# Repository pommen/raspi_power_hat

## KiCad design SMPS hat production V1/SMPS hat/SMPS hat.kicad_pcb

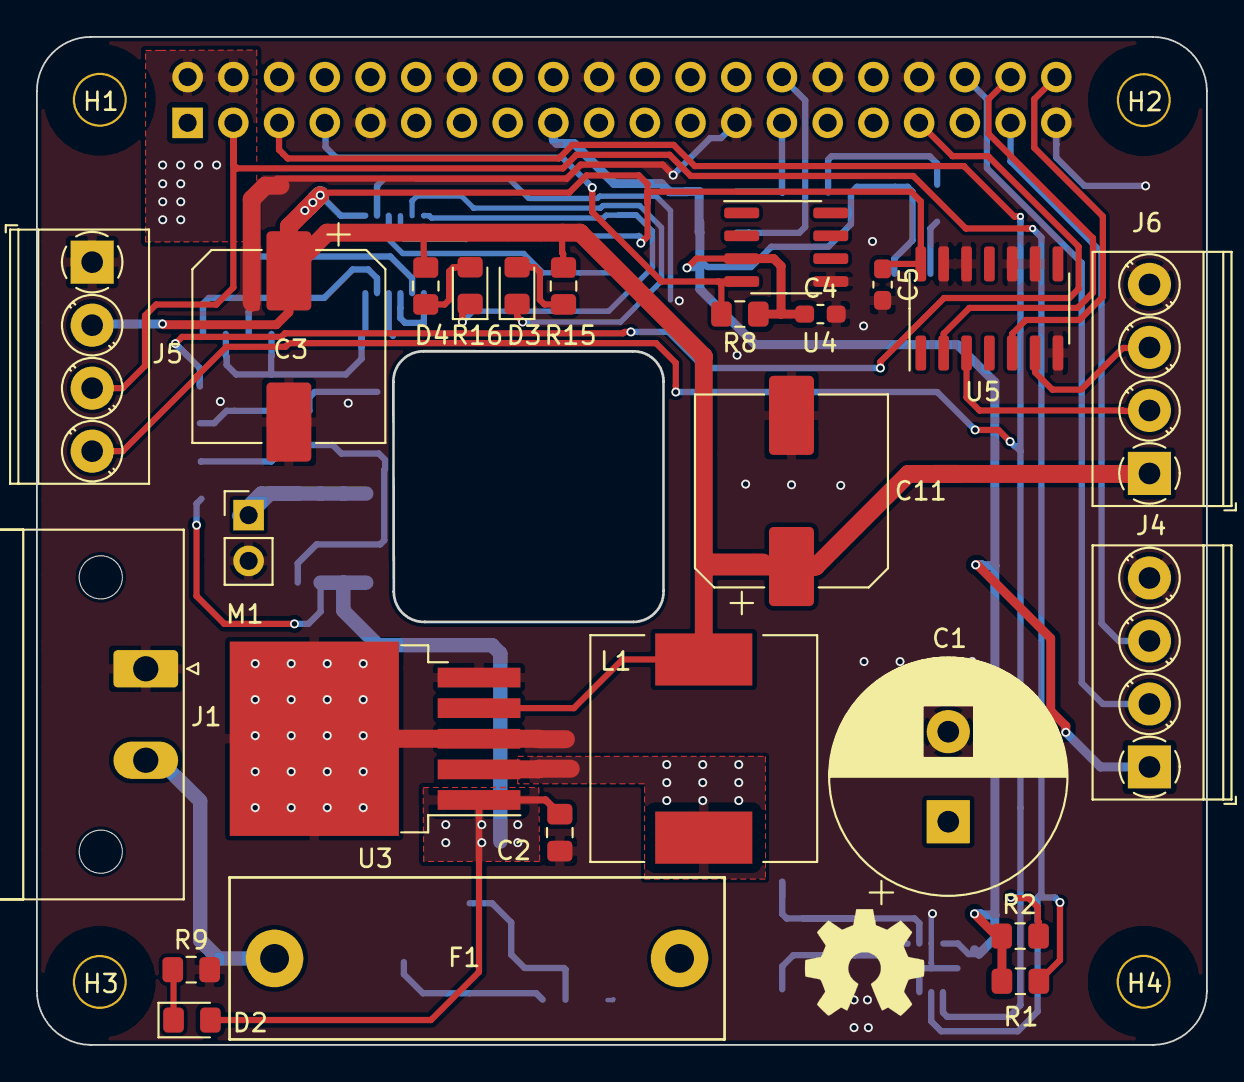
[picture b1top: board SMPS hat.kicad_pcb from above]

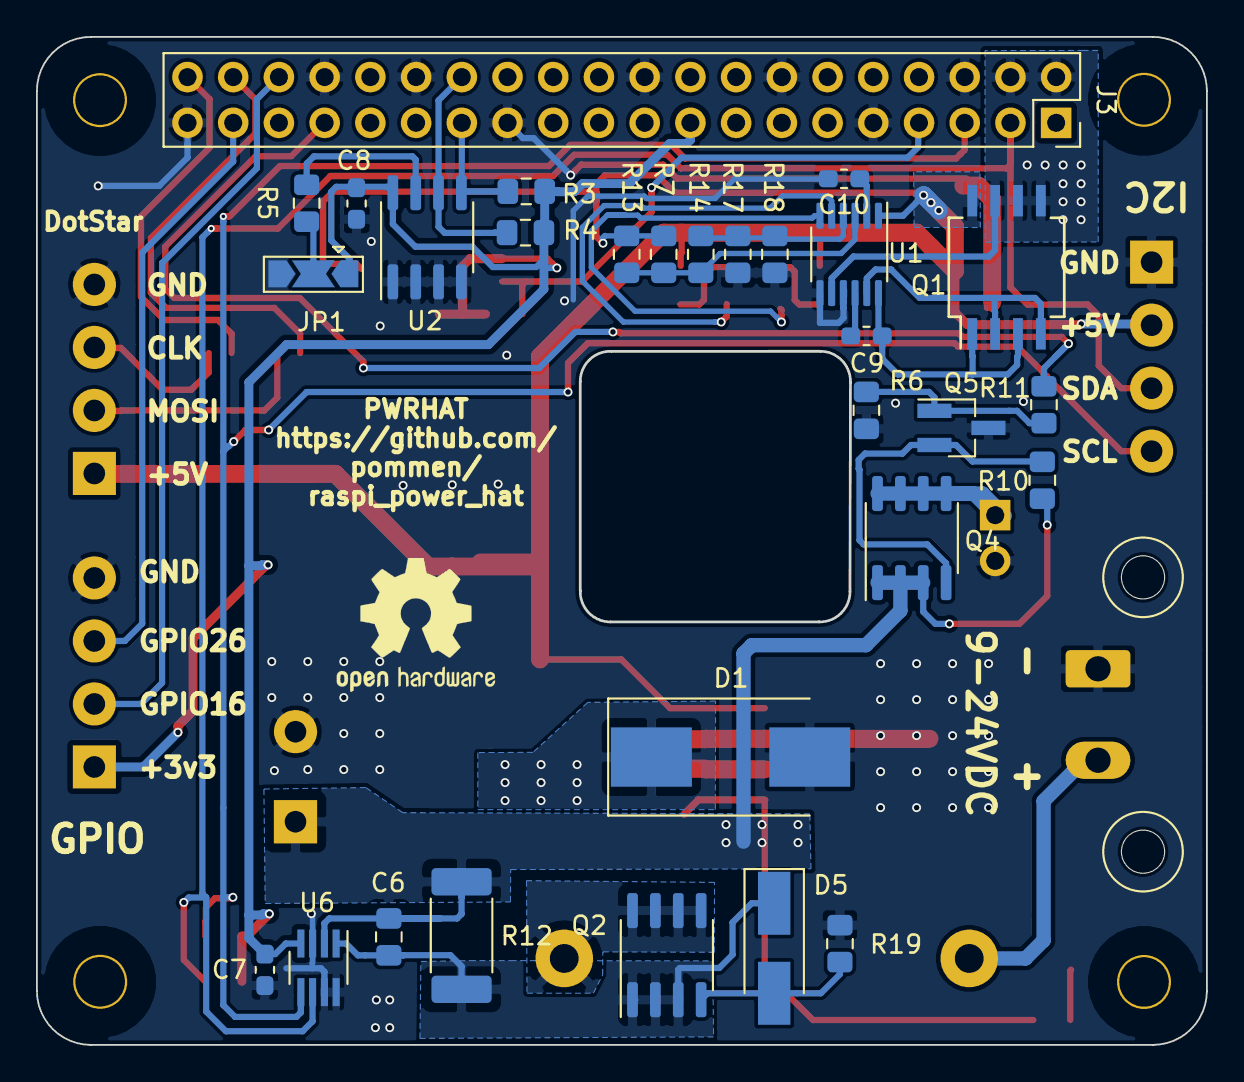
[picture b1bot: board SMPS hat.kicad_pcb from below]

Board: 2 copper layers, 65.0 x 56.0 mm, 58 parts (29 on the bottom side), 38 nets.

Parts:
C1: 100uF 50V; CP_Radial_D13.0mm_P5.00mm
C2: 100nF 50V; C_0805_2012Metric_Pad1.15x1.40mm_HandSolder
C3, C11: 470uF25V; CP_Elec_10x10.5
C4, C5, C8, C9, C10: 100n; C_0603_1608Metric_Pad1.05x0.95mm_HandSolder
C6: 1n; C_0805_2012Metric_Pad1.15x1.40mm_HandSolder
C7: C; C_0603_1608Metric_Pad1.05x0.95mm_HandSolder
D1: D_Schottky; D_SMC_Handsoldering
D2, D3, D4: LED; LED_0805_2012Metric_Pad1.15x1.40mm_HandSolder
D5: 10V; D_SMA_Handsoldering
F1: 5A; Fuse_holser_Plastic_ebay
H1, H2, H3, H4: 3mm_Mounting_Hole; NPTH_3mm_ID
J1: Vin; PhoenixContact_MSTB_2,5_2-GF-5,08_1x02_P5.08mm_Horizontal_T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
J3: 40HAT; PinSocket_2x20_P2.54mm_Vertical
J4: GPIO; TerminalBlock_Phoenix_PT-1,5-4-3.5-H_1x04_P3.50mm_Horizontal
J5: DISP; TerminalBlock_Phoenix_PT-1,5-4-3.5-H_1x04_P3.50mm_Horizontal
J6: DotStar; TerminalBlock_Phoenix_PT-1,5-4-3.5-H_1x04_P3.50mm_Horizontal
JP1: Write ena; SolderJumper-3_P2.0mm_Open_TrianglePad1.0x1.5mm
L1: 100uH; L_12x12mm_H8mm
M1: Fan; PinHeader_1x02_P2.54mm_Vertical
Q1: Si4804; SO-8_5.3x6.2mm_P1.27mm
Q2, Q4: Si4435; SOIC-8_3.9x4.9mm_P1.27mm
Q5: BSS138; SOT-23_Handsoldering
R1, R2, R8: 4k7; R_0805_2012Metric_Pad1.15x1.40mm_HandSolder
R3, R4: 3.9K; R_0805_2012Metric_Pad1.15x1.40mm_HandSolder
R5, R9, R10: 10K; R_0805_2012Metric_Pad1.15x1.40mm_HandSolder
R6: 62K; R_0805_2012Metric_Pad1.15x1.40mm_HandSolder
R7, R17: DNP; R_0805_2012Metric_Pad1.15x1.40mm_HandSolder
R11: 1K; R_0805_2012Metric_Pad1.15x1.40mm_HandSolder
R12: 0R1; R_2512_6332Metric_Pad1.52x3.35mm_HandSolder
R13: 31.6k 1%; R_0805_2012Metric_Pad1.15x1.40mm_HandSolder
R14: 1k 1%; R_0805_2012Metric_Pad1.15x1.40mm_HandSolder
R15, R16: R; R_0805_2012Metric_Pad1.15x1.40mm_HandSolder
R18: 3K09 1%; R_0805_2012Metric_Pad1.15x1.40mm_HandSolder
R19: 60K; R_0805_2012Metric_Pad1.15x1.40mm_HandSolder
U1: LTC4352; MSOP-12_3x4mm_P0.65mm
U2: M24C01-WMN; SOIC-8_3.9x4.9mm_P1.27mm
U3: LM2576HVS-5; TO-263-5_TabPin3
U4: DS18S20Z; SOIC-8_3.9x4.9mm_P1.27mm
U5: 74LVC125; SOIC-14_3.9x8.7mm_P1.27mm
U6: INA219; SOT-23-8_Handsoldering

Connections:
+3V3: C4.1, C7.1, C8.1, J3.1, J3.17, J4.1, JP1.1, R1.1, R2.1, R3.1, R4.1, R8.1, U2.8, U4.3, U6.4
+5V: C3.1, C5.1, C11.1, J5.2, J6.1, L1.2, Q1.8, R7.1, R13.1, R15.1, R16.1, U1.1, U3.4, U5.14
+24V: C1.1, C2.1, C6.1, D2.2, Q4.1, Q4.2, Q4.3, R10.1, R12.1, U3.1, U6.2
/DotStar_clock: J6.3, U5.6
/Dotstar_data: J6.2, U5.3
/GPIO16: J3.36, J4.2
/GPIO26: J3.37, J4.3
/Hat power/VIN: F1.2, J1.2
/ID_SC_EEPROM: J3.28, R4.2, U2.6
/ID_SD_EEPROM: J3.27, R3.2, U2.5
/LED_MOSI: J3.38, U5.2
/LED_SCLK: J3.40, U5.5
/P5V_HAT: J3.2, J3.4, Q1.5, Q1.6, Q1.7, U1.8
/PWM_FAN: J3.33, R11.1
/SCL: J3.5, J5.4, R2.2, U6.5
/SDA: J3.3, J5.3, R1.2, U6.6
/temp: J3.7, R8.2, U4.4
GND: C1.2, C2.2, C3.2, C4.2, C5.2, C7.2, C8.2, C10.2, C11.2, D1.2, J1.1, J3.6, J3.9, J3.14, J3.20, J3.25, J3.30, J3.34, J3.39, J4.4, J5.1, J6.4, JP1.3, M1.2, Q5.3, R6.2, R9.2, R17.2, R18.2, R19.2, U1.7, U1.9, U2.1, U2.2, U2.3, U2.4, U3.3, U3.5, U4.5, U5.7, U5.9, U5.10, U5.12, U5.13, U6.3, U6.7, U6.8
unnamed: C6.2, D5.1, Q2.1, Q2.2, Q2.3, R12.2, U6.1
unnamed: C9.1, Q1.1, Q1.3, U1.12
unnamed: C9.2, U1.10
unnamed: C10.1, U1.2
unnamed: D1.1, L1.1, U3.2
unnamed: D2.1, R9.1
unnamed: D3.1, U1.5
unnamed: D3.2, R15.2
unnamed: D4.1, U1.6
unnamed: D4.2, R16.2
unnamed: D5.2, Q2.4, R19.1
unnamed: F1.1, Q2.5, Q2.6, Q2.7, Q2.8
unnamed: JP1.2, R5.2
unnamed: M1.1, Q4.5, Q4.6, Q4.7, Q4.8
unnamed: Q1.2, Q1.4, U1.11
unnamed: Q4.4, Q5.2, R10.2
unnamed: Q5.1, R6.1, R11.2
unnamed: R5.1, U2.7
unnamed: R7.2, R13.2, R14.1, U1.3
unnamed: R14.2, R17.1, R18.1, U1.4

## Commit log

2019-08-03 First sync
2019-08-04 sync
